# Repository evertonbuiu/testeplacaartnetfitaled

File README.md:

# Welcome to your Lovable project

## Project info

**URL**: https://lovable.dev/projects/0b61df0e-4494-4a09-8b1f-411c505e3504

## How can I edit this code?

There are several ways of editing your application.

**Use Lovable**

Simply visit the [Lovable Project](https://lovable.dev/projects/0b61df0e-4494-4a09-8b1f-411c505e3504) and start prompting.

Changes made via Lovable will be committed automatically to this repo.

**Use your preferred IDE**

If you want to work locally using your own IDE, you can clone this repo and push changes. Pushed changes will also be reflected in Lovable.

The only requirement is having Node.js & npm installed - [install with nvm](https://github.com/nvm-sh/nvm#installing-and-updating)

Follow these steps:

```sh
# Step 1: Clone the repository using the project's Git URL.
git clone <YOUR_GIT_URL>

# Step 2: Navigate to the project directory.
cd <YOUR_PROJECT_NAME>

# Step 3: Install the necessary dependencies.
npm i

# Step 4: Start the development server with auto-reloading and an instant preview.
npm run dev
```

**Edit a file directly in GitHub**

- Navigate to the desired file(s).
- Click the "Edit" button (pencil icon) at the top right of the file view.
- Make your changes and commit the changes.

**Use GitHub Codespaces**

- Navigate to the main page of your repository.
- Click on the "Code" button (green button) near the top right.
- Select the "Codespaces" tab.
- Click on "New codespace" to launch a new Codespace environment.
- Edit files directly within the Codespace and commit and push your changes once you're done.

## What technologies are used for this project?

This project is built with:

- Vite
- TypeScript
- React
- shadcn-ui
- Tailwind CSS

## How can I deploy this project?

Simply open [Lovable](https://lovable.dev/projects/0b61df0e-4494-4a09-8b1f-411c505e3504) and click on Share -> Publish.

## Can I connect a custom domain to my Lovable project?

Yes, you can!

To connect a domain, navigate to Project > Settings > Domains and click Connect Domain.

Read more here: [Setting up a custom domain](https://docs.lovable.dev/tips-tricks/custom-domain#step-by-step-guide)

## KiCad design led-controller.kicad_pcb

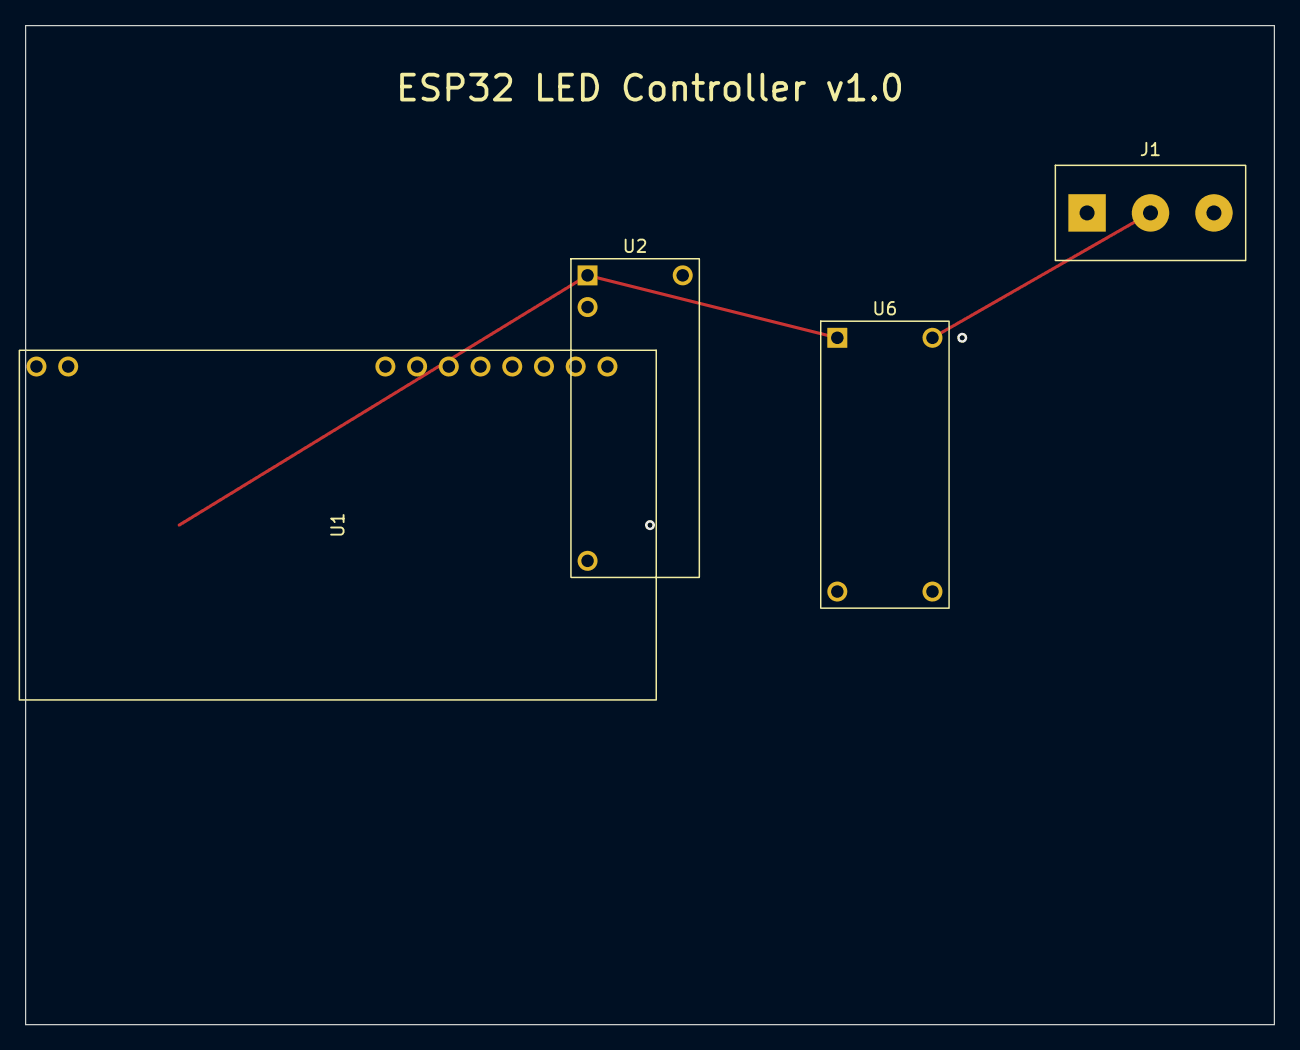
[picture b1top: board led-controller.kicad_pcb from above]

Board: 2 copper layers, 100.0 x 80.0 mm, 4 parts (0 on the bottom side), 4 nets.

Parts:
J1: LED_OUT_1; TerminalBlock_bornier-3_P5.08mm
U1: ESP32-DevKitC
U2: 74HCT245; DIP-20_W7.62mm
U6: ULN2803A; DIP-18_W7.62mm

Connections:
GND: J1.3, U1.1 (GND), U2.1 (A->B), U2.10 (GND), U6.10 (GND)
GPIO2: U1.10 (GPIO2), U2.2 (A0), U6.1 (I1)
LED_OUT_1: J1.2, U6.18 (O1)
VCC: J1.1, U1.2 (3V3), U2.20 (VCC), U6.9 (VCC)

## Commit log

2025-07-19 Use tech stack vite_react_shadcn_ts
2025-07-19 Implement LED strip system
    Implement a system for WS2811 LED strips with 32 outputs, Art-Net control, manual configuration, and a digital display.
2025-07-19 Show PCB image
    Add a PCB image to the application.
2025-07-19 Add Art-Net IP configuration
    Add Art-Net IP configuration options to the settings.
2025-07-19 Add IP mode selection
    Allow selection between auto, broadcast, and fixed IP modes.
2025-07-19 Separate display and buttons
    Move the display and command buttons to a separate board, connected to the central board via a flat cable.
2025-07-19 Separate physical outputs into boards
    Separate 32 physical outputs into 4 separate boards connected to the central board via flat cables and born connectors.
2025-07-19 Connect to Supabase project
    Add Supabase configuration and types to the project.
2025-07-19 Add LED IC type configuration
    Allow selecting different LED IC types via the display.
2025-07-19 Show display PCB image
    Show the image of both sides of the display PCB.
2025-07-19 Add improved display
    Implement a larger, higher-quality display with physical buttons and a touchscreen.
2025-07-19 Add support for 3 and 4 pin LED strips
    Update output boards to support both 3-pin and 4-pin LED strips.
2025-07-19 Update output PCB
    Modify the output PCB to arrange the terminals in a single row for box mounting, with terminals accessible for LED strip connections.
2025-07-19 Improve main board quality
    Add network connectors with LEDs.
2025-07-19 Show display configurations.
    Show all configurations on the display for setup.
2025-07-19 Add output configuration options
    Add options to configure outputs and universes.
2025-07-19 Fix output configuration
    Update the output configuration to show all 32 outputs.
2025-07-19 Configure universes per output
    Allow configuration of 1 to 8 universes per physical output.
2025-07-19 Add test option
    Add a test option to test the RGB of each physical output.
2025-07-19 Fix test menu
    The test menu should show all outputs. Add manual RGB control option.
2025-07-19 Add option to select all outputs
    Add an option to select all outputs.
2025-07-19 Add pre-made effects
    Create pre-made effects for use.
2025-07-19 Add running color effect
    Implement a running color effect with customizable colors and pixel blocks.
2025-07-19 Add reset and factory default functions
    Implement reset and factory default functions in the system settings.
2025-07-19 Add system status display
    Show system status on main display.
2025-07-19 Update LED voltage support
    Change the system to support LED strips from 05V to 024V.
2025-07-19 Implement output board amplifier.
2025-07-19 Describe output PCB connections.
    Add information about how output PCBs connect to the main board.
2025-07-19 Generate EasyEDA file.
    Create a complete file for EasyEDA.
2025-07-19 Create EasyEDA project
    Create a complete EasyEDA project with correct components and all information.
2025-07-19 Fix EasyEDA format issue
2025-07-19 Generate Gerber files
    Generate Gerber files for manufacturing.
2025-07-19 Open project in KiCad
    Instructions on how to open the project in KiCad.
2025-07-19 Add component information
    Include real component information in the project file.
2025-07-19 Fix KiCad schema loading error
    Correct KiCad schema loading error.
2025-07-19 Fix KiCad schema error
    Corrected KiCad schema error.
2025-07-19 Fix missing electronic components
    Update KiCad project to include all components.
2025-07-19 Add missing components
    Complete the KiCad schematic with all required electronic components.
2025-07-20 Add missing components to KiCad
    Ensure all components are present in the KiCad schematic.
2025-07-20 Fix KiCad schematic error
    Fix error loading KiCad schematic file.
2025-07-20 Add interactive viewer
    Implement an interactive viewer to display schematic, PCB, and 3D representations in a more sophisticated manner.
2025-07-20 Fix build errors
    Resolve "SRGBColorSpace" and "LinearSRGBColorSpace" import errors.
2025-07-28 Add Celus project support
    Create a new route and page for the Celus project, allowing it to be opened on the Celus website.
2025-08-17 Fix: Resolve undefined 'lov' error
    The error "Uncaught TypeError: Cannot read properties of undefined (reading 'lov')" indicates an issue with how data is being processed or accessed within the interactive viewer component. This is li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
2025-08-17 Fix: Resolve runtime error
    The `componentTagger` in `vite.config.ts` was disabled to fix a runtime error related to undefined 'lov' properties, likely caused by conflicts with Three.js components.
